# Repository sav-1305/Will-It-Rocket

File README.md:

# Will It Rocket?

Repository for all programs and software developed by the **Avionics** Subsystem of **ThrustMIT 2025**. 🚀

## REPOSITORY CONTENTS
- *`Docs`*             : Documents made or referenced during tenure
- *`Driver Code`*      : Libraries developed for specific projects/general-purpose for various microcontrollers and systems
- *`Libraries`*        : Object-Oriented libraries for sensor Modules
- *`Motor Test 23`*    : Project Repository for the software developed for the Motor Test project undertaken by Avionics Team 2023-24.
- *`PCB Projects`*     : PCB KiCAD project files developed for projects, along with footprints and symbol libraries.
- *`Test Projects`* : sketch files for projects/programs used for testing in various projects developed during our tenure. 
## MOTOR TEST
Provided is the Link to the general-purpose repository dedicated for the final programs, testing, and documentation associated with the [MOTOR TEST](https://github.com/TMIT-Avionics/TMIT_MOTORTEST23) held on November 6, 2023.

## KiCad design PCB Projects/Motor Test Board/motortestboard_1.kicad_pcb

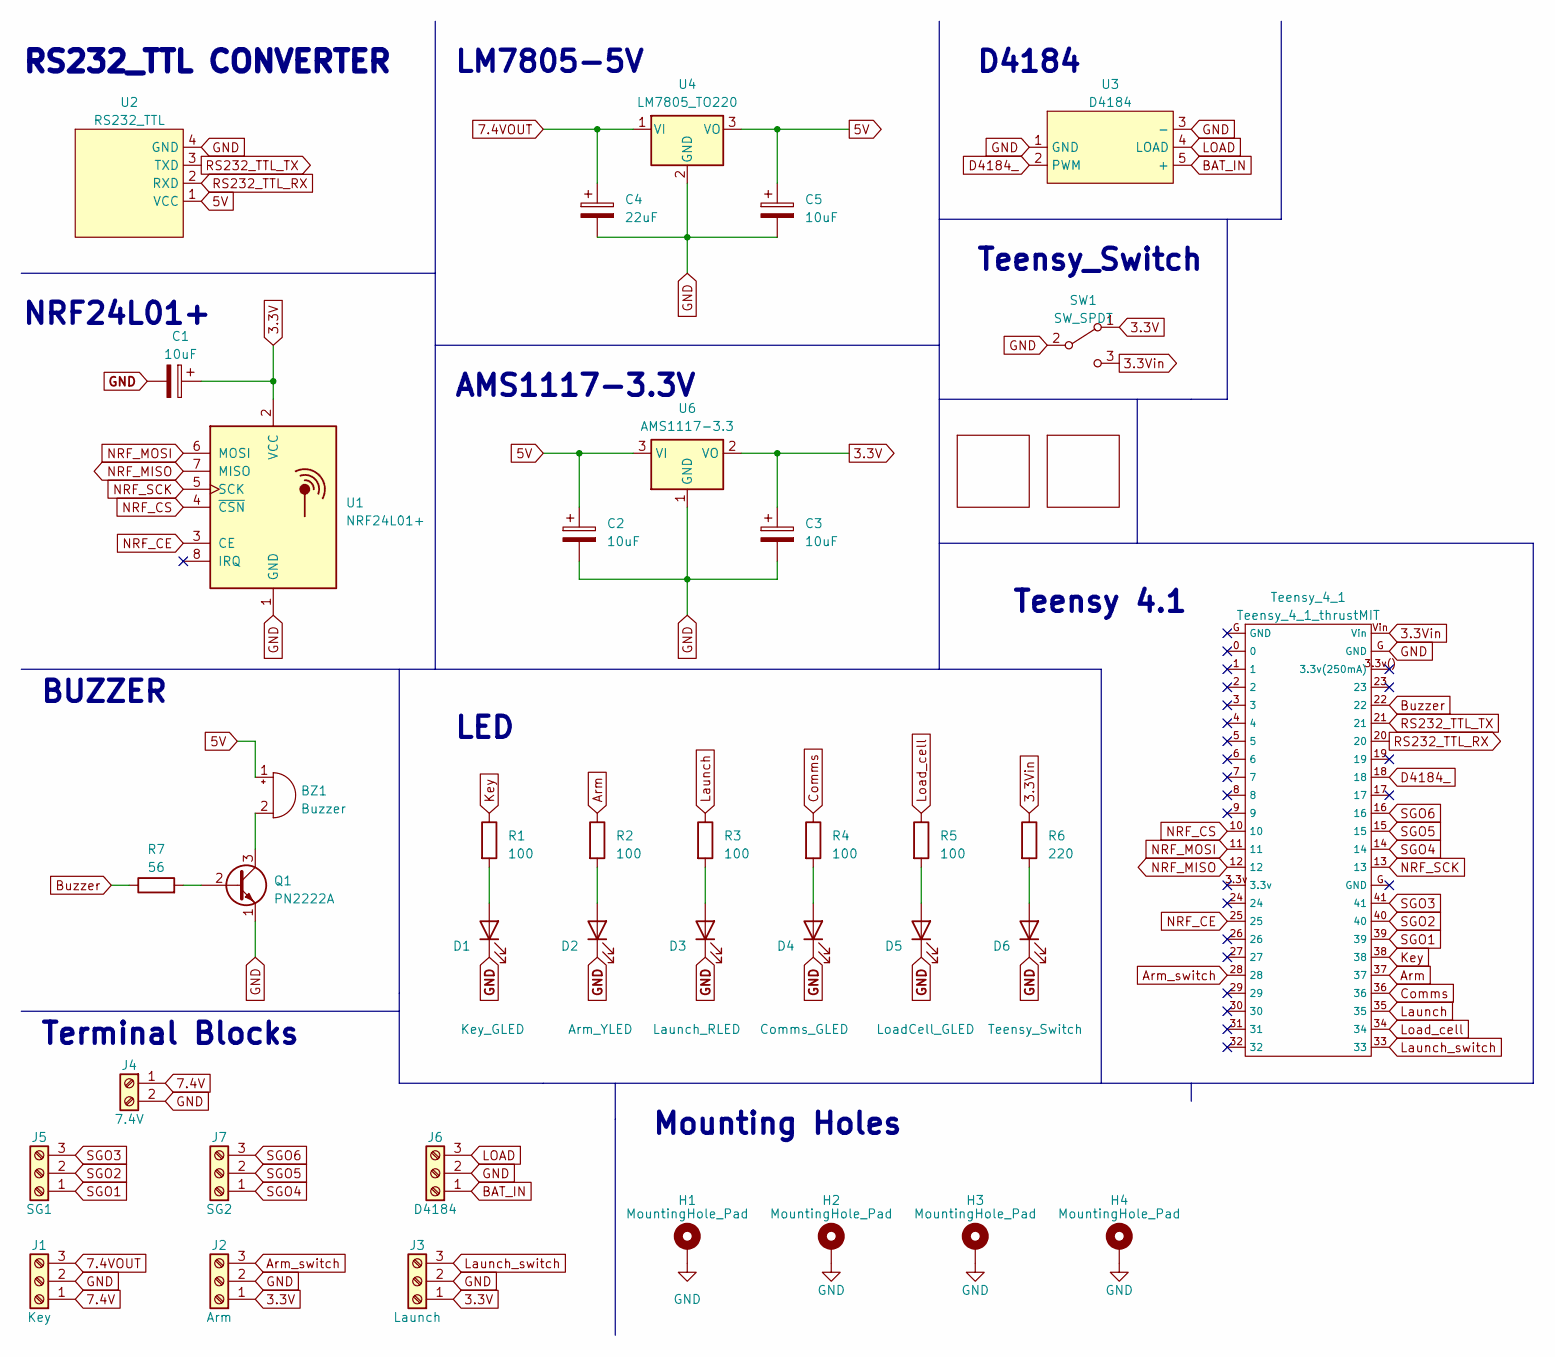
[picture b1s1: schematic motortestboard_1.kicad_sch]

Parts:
BZ1: Buzzer; MagneticBuzzer_ProSignal_ABT-410-RC
C1, C2, C3, C5: 10uF; CP_Radial_D5.0mm_P2.00mm
C4: 22uF; CP_Radial_D5.0mm_P2.00mm
D1: Key_GLED; LED_D5.0mm
D2: Arm_YLED; LED_D5.0mm
D3: Launch_RLED; LED_D5.0mm
D4: Comms_GLED; LED_D5.0mm
D5: LoadCell_GLED; LED_D5.0mm
D6: Teensy_Switch; LED_D5.0mm
H1, H2, H3, H4: MountingHole_Pad; MountingHole_4.3mm_M4_Pad
J1: Key; TerminalBlock_bornier-3_P5.08mm
J2: Arm; TerminalBlock_bornier-3_P5.08mm
J3: Launch; TerminalBlock_bornier-3_P5.08mm
J4: 7.4V; TerminalBlock_bornier-2_P5.08mm
J5: SG1; TerminalBlock_bornier-3_P5.08mm
J6: D4184; TerminalBlock_bornier-3_P5.08mm
J7: SG2; TerminalBlock_bornier-3_P5.08mm
Q1: PN2222A; TO-92_Inline
R1, R2, R3, R4, R5: 100; R_Axial_DIN0204_L3.6mm_D1.6mm_P5.08mm_Horizontal
R6: 220; R_Axial_DIN0204_L3.6mm_D1.6mm_P5.08mm_Horizontal
R7: 56; R_Axial_DIN0204_L3.6mm_D1.6mm_P5.08mm_Horizontal
SW1: SW_SPDT; EG1218
Teensy_4_1: Teensy_4_1_thrustMIT
U1: NRF24L01+; nrf24l01+
U2: RS232_TTL
U3: D4184
U4: LM7805_TO220; TO-220-3_Vertical
U5: LOGO_03
U6: AMS1117-3.3; SOT-223-3_TabPin2
U7: LOGO__01

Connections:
3.3V: C1.1, C3.1, J2.1, J3.1, SW1.1 (A), U1.2 (VCC), U6.2 (VO)
3.3Vin: R6.1, SW1.3 (C), Teensy_4_1.Vin
5V: BZ1.1 (-), C2.1, C5.1, U2.1 (VCC), U4.3 (VO), U6.3 (VI)
7.4V: J1.1, J4.1
7.4VOUT: C4.1, J1.3, U4.1 (VI)
Arm: R2.1, Teensy_4_1.37
Arm_switch: J2.3, Teensy_4_1.28
BAT_IN: J6.1, U3.5 (+)
Buzzer: R7.1, Teensy_4_1.22
Comms: R4.1, Teensy_4_1.36
D4184_: Teensy_4_1.18, U3.2 (PWM)
GND: C1.2, C2.2, C3.2, C4.2, C5.2, D1.1 (K), D2.1 (K), D3.1 (K), D4.1 (K), D5.1 (K), D6.1 (K), H1.1, H2.1, H3.1, H4.1, J1.2, J2.2, J3.2, J4.2, J6.2, Q1.1 (E), SW1.2 (B), Teensy_4_1.G (GND), U1.1 (GND), U2.4 (GND), U3.1 (GND), U3.3 (-), U4.2 (GND), U6.1 (GND)
Key: R1.1, Teensy_4_1.38
LOAD: J6.3, U3.4 (LOAD)
Launch: R3.1, Teensy_4_1.35
Launch_switch: J3.3, Teensy_4_1.33
Load_cell: R5.1, Teensy_4_1.34
NRF_CE: Teensy_4_1.25, U1.3 (CE)
NRF_CS: Teensy_4_1.10, U1.4 (~CSN)
NRF_MISO: Teensy_4_1.12, U1.7 (MISO)
NRF_MOSI: Teensy_4_1.11, U1.6 (MOSI)
NRF_SCK: Teensy_4_1.13, U1.5 (SCK)
unnamed: BZ1.2 (+), Q1.3 (C)
unnamed: D1.2 (A), R1.2
unnamed: D2.2 (A), R2.2
unnamed: D3.2 (A), R3.2
unnamed: D4.2 (A), R4.2
unnamed: D5.2 (A), R5.2
unnamed: D6.2 (A), R6.2
unnamed: Q1.2 (B), R7.2
RS232_TTL_RX: Teensy_4_1.20, U2.2 (RXD)
RS232_TTL_TX: Teensy_4_1.21, U2.3 (TXD)
SGO1: J5.1, Teensy_4_1.39
SGO2: J5.2, Teensy_4_1.40
SGO3: J5.3, Teensy_4_1.41
SGO4: J7.1, Teensy_4_1.14
SGO5: J7.2, Teensy_4_1.15
SGO6: J7.3, Teensy_4_1.16

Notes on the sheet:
Mounting Holes
D4184
Teensy 4.1
BUZZER
LM7805-5V
RS232_TTL CONVERTER
AMS1117-3.3V
NRF24L01+
Teensy_Switch
LED
Terminal Blocks

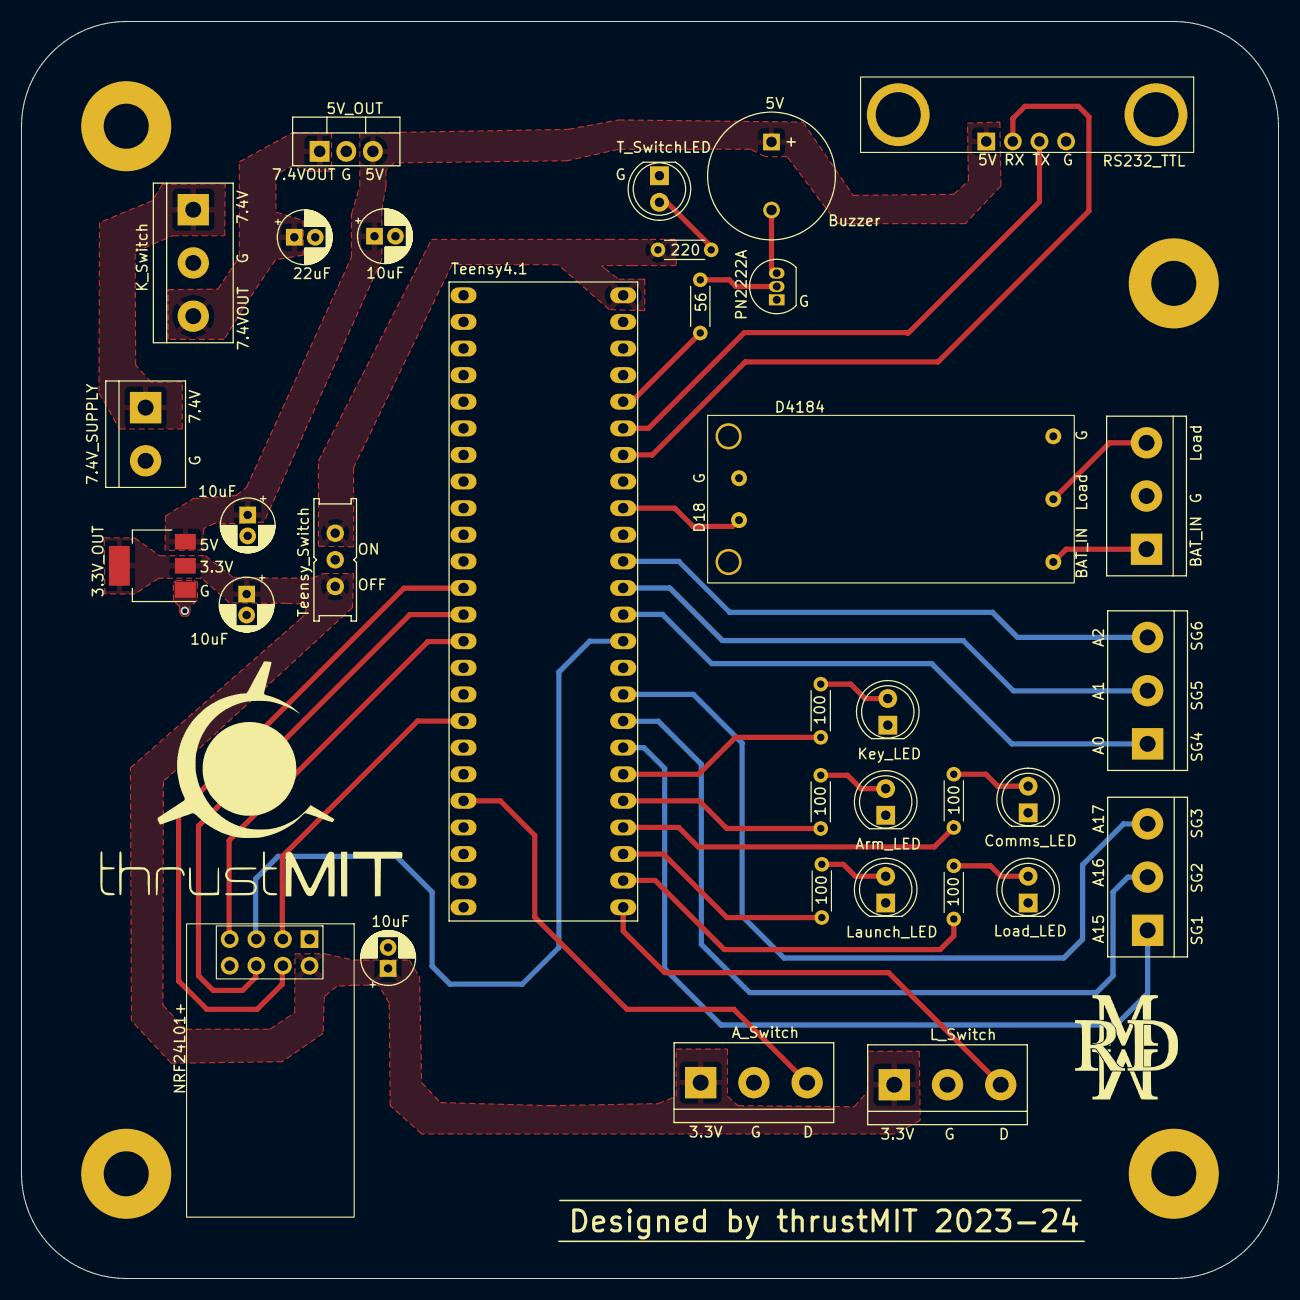
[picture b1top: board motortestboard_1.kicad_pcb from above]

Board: 2 copper layers, 120.0 x 120.0 mm, 40 parts (0 on the bottom side), 38 nets.

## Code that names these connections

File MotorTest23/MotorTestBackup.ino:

/* MOTOR TEST BACKUP - ARDUINO IDE
    program written as backup for motor-test project - MOTOR SIDE - in arduino IDE due to
    complexities in PlatformIO.
    Designed for Teensy 4.1
    Peripherals - 
                  nRF24L01
                  BF350-Strain Gauge
                  Load Cell
    
    Written for ThrustMIT Avionics 23-24.
*/

/* INCLUDES */

#include <SD.h>
#include <SPI.h>
#include <RF24.h>
#include <nRF24L01.h>
#include <string.h>

/* MACROS */

#define D1      5
#define D2      6
#define CE_PIN  9
#define CSN_PIN 10
#define ANALOG  A5
#define loadSerial Serial5

#define KEY     38
#define ARM     37
#define LAUNCH  35
#define COMMS   36
#define LOAD    34

/* VARIABLES */

const byte address[2][6] = {"00000", "00001"};  //Addresses for nRFs
char receive[32];                               //array buffers for transmission data
char transmit[32];
RF24 radio(CE_PIN, CSN_PIN);
bool isLaunched = false;

//static int logCount = 0;                        //Only for testing purposes
File logFile;

int wheatStone = 0;
float voltage = 0, strain = 0;                  //Strain is final straingauge output

/* MACROS FOR STRAIN CALCULATION:
      Gauge Factor = 2-2.0
      Excitation Voltage = 5V
      Reference max voltage = 3.5V

      analog - digital conversion => voltage = wheatStone (analog reading) * 3.5 / 1023;
      strain = voltage * 0.4
*/

struct SensorData {
  float load;
  float strain;
} Data;

float loadBuffer = 0;
float loadCellOutput = 0;
float strainGaugeOutput = 0;

enum STATE {
  SAFE,
  ARMED,
  LAUNCHED,
  HALTED
};

STATE currentState = SAFE;

/* FUNCTIONS */

float readLoadCell() {
  if (loadSerial.available()) {
    loadBuffer = loadSerial.read();
    Data.load = loadBuffer;
    return loadBuffer;
  }
  return -1;
}

float calculate() {
  wheatStone = analogRead(ANALOG);
  voltage = 3.5 * wheatStone / 1023;
  strain = 0.4 * voltage;
  Data.strain = strain;
  return strain;
}

void logData(float load, float strain) {

  logFile = SD.open("motorTest.csv", FILE_WRITE);

  if (logFile) {
    logFile.print(load);
    logFile.print(",");
    logFile.println(strain);
    logFile.close();
    Serial.println("DATA LOGGED SUCCESSFULLY. ");
  }
}

void checkInput(char buffer[]) {
  if ((strcmp(buffer, "ARM_ON") == 0) && (currentState == SAFE)) {
    currentState = ARMED;
    Serial.println("Current state: ARMED");
    return;
  }
  else if ((strcmp(buffer, "LAUNCH") == 0) && (currentState == ARMED)) {
    currentState = LAUNCHED;
    Serial.println("Current state: LAUNCHED");
    return;
  }
  else if ((strcmp(buffer, "ARM_OFF") == 0) && (currentState == ARMED)) {
    currentState = SAFE;
    Serial.println("Current state: SAFE");
    return;
  }
  else if ((strcmp(buffer, "FAILURE") == 0) && (currentState == ARMED)) {
    currentState = HALTED;
    Serial.println("Current state: HALTED");
    return;
  }
  else if ((strcmp(buffer, "FAILURE") == 0) && (currentState == SAFE)) {
    currentState = HALTED;
    Serial.println("Current state: HALTED");
    return;
  }
  else if ((strcmp(buffer, "FAILURE") == 0) && (currentState == LAUNCHED)) {
    currentState = HALTED;
    Serial.println("Current state: HALTED");
    return;
  }
  else if ((strcmp(buffer, "SAFE") == 0) && (currentState == HALTED)) {
    currentState = SAFE;
    Serial.println("Current state: SAFE");
    return;
  }
  else {
    Serial.println("Invalid Input Provided to Motor System. ");
  }
}

STATE getCurrentState() {
  return currentState;
}

void DataTelemetry(SensorData Data) {

  radio.write(&Data, sizeof(SensorData));

}

void performOperation(STATE s) {
  switch(s) {
    case SAFE:

      digitalWrite(KEY, HIGH);
      delay(1000);
      digitalWrite(KEY, LOW);
      delay(1000);
      break;

    case ARMED:

      digitalWrite(KEY, HIGH);

      strainGaugeOutput = calculate();
      loadCellOutput = readLoadCell();
      logData(loadCellOutput, strainGaugeOutput);

      digitalWrite(ARM, HIGH);
      delay(1000);
      digitalWrite(ARM, LOW);
      delay(1000);
      break;

    case LAUNCHED:

      if (!isLaunched) {
        radio.openWritingPipe(address[1]);
        radio.stopListening();
        isLaunched = true;
      }

      strainGaugeOutput = calculate();
      loadCellOutput = readLoadCell();
      logData(loadCellOutput, strainGaugeOutput);

      DataTelemetry(Data);

      digitalWrite(KEY, HIGH);
      digitalWrite(ARM, HIGH);

      digitalWrite(LAUNCH, HIGH);
      delay(1000);
      digitalWrite(LAUNCH, LOW);
      delay(1000);
      break;

    case HALTED:

      digitalWrite(LAUNCH, HIGH);
      delay(200);
      digitalWrite(LAUNCH, LOW);
      delay(200);
      logFile.close();
      break;

    default:
      break;
  }
}

void setup() {

  Serial.begin(9600);
  Serial.println("1. SERIAL COMMS : INITIALISED");

  pinMode(KEY, OUTPUT);
  pinMode(ARM, OUTPUT);
  pinMode(LAUNCH, OUTPUT);
  pinMode(COMMS, OUTPUT);
  pinMode(LOAD, OUTPUT);
  Serial.println("    NOTE: LEDs configured. ");

  
  if (!radio.begin()) {
    Serial.println("2. NRF COMMS: FAILED");
  }
  else {
    Serial.println("2. NRF COMMS: INITIALISED");
  }
  radio.openReadingPipe(1, address[0]);
  radio.setPALevel(RF24_PA_MIN);
  radio.startListening();


  if (!SD.begin(BUILTIN_SDCARD)) {
    Serial.println("3. SD CARD: FAILED");
  } 
  else {
    Serial.println("3. SD CARD: INITIALISED");
  }

  if (SD.exists("motorTest.csv")) {
    SD.remove("motorTest.csv");
    Serial.println("  3(a) File refreshed. ");
  }

  logFile = SD.open("motorTest.csv", FILE_WRITE);
  if (logFile) {
    logFile.println("Load,Strain");
    Serial.println("  3(b) File created. ");
    logFile.close();
  }
  else {
    Serial.println("  3(b) unable to setup file. LOGGING FAILED. ");
    logFile.close();
  }

}

void loop() {

  if (radio.available()) {
    radio.read(receive, sizeof(receive));
    Serial.print("Received Data: ");
    Serial.println(receive);

    checkInput(receive);
  }

  performOperation(getCurrentState());

}

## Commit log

2023-04-26 Create datasheet list
2023-04-26 Rename datasheet list to list.md
2023-04-26 Rename NRF24L01Rx.ino to NRF/NRF24L01Rx.ino
2023-04-29 Create SensorCode
2023-05-04 Create MPU6050SensData
2023-05-04 Update MPU6050SensData
2023-05-05 Create MPU6050SensDataTimerDelay
2023-05-15 Create mpu6050.h
    header file for I2C MPU6050 Driver; Designed for STM32F4 HAL
2023-05-15 Create mpu6050.c
    source file for I2C MPU6050 Driver; Designed for STM32F4 HAL
2023-05-15 Rename mpu6050.c to mpu6050.c
2023-05-15 Rename mpu6050.h to mpu6050.h
2023-07-22 edit 1
2023-09-04 motor
2023-09-20 Rename BF350Test/BF350Test.ino to Test Projects/BF350Test/BF350Test.ino
2023-09-20 Rename SDcardTest/SDcardTest.ino to Test Projects/SDcardTest/SDcardTest.ino
2023-10-01 Create deleteme
2023-10-08 added folders
2023-10-14 added backup for motorcode - motor side
2023-10-14 Add files via upload
    //backup on arduino ide
2023-10-14 Create motorTestgroundBackup
2023-10-14 Rename motorTestgroundBackup to motorTestgroundBackup.ino
2023-10-18 organised
2023-10-18 doc sorting
2023-10-19 Create Motor Test Board
2023-10-19 Create revised
2024-04-10 added ignition
2024-04-10 added DD code
2024-04-11 name changed
